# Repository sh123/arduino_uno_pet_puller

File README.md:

# Arduino plastic bottle to PET filament puller
This project is Arduino UNO/Duemilanove shield and minimalistic firmware for "Petalot PET Bottle to 3D filament" or another device with similar mechanics.

For more information about Petalot and its construction read at https://github.com/function3d/petalot.

This alternative board version based on parts and components found in a junk box, such as old Arduino UNO/Duemilanove, MX1508 stepper controller, external 12-13V power suppply, EM257 stepper from old printer, unlike origintal version it does not use WiFi remote control.

NB! PCB board is designed to be suitable for CNC milling, so some layout design decisions might look somewhat illogical.

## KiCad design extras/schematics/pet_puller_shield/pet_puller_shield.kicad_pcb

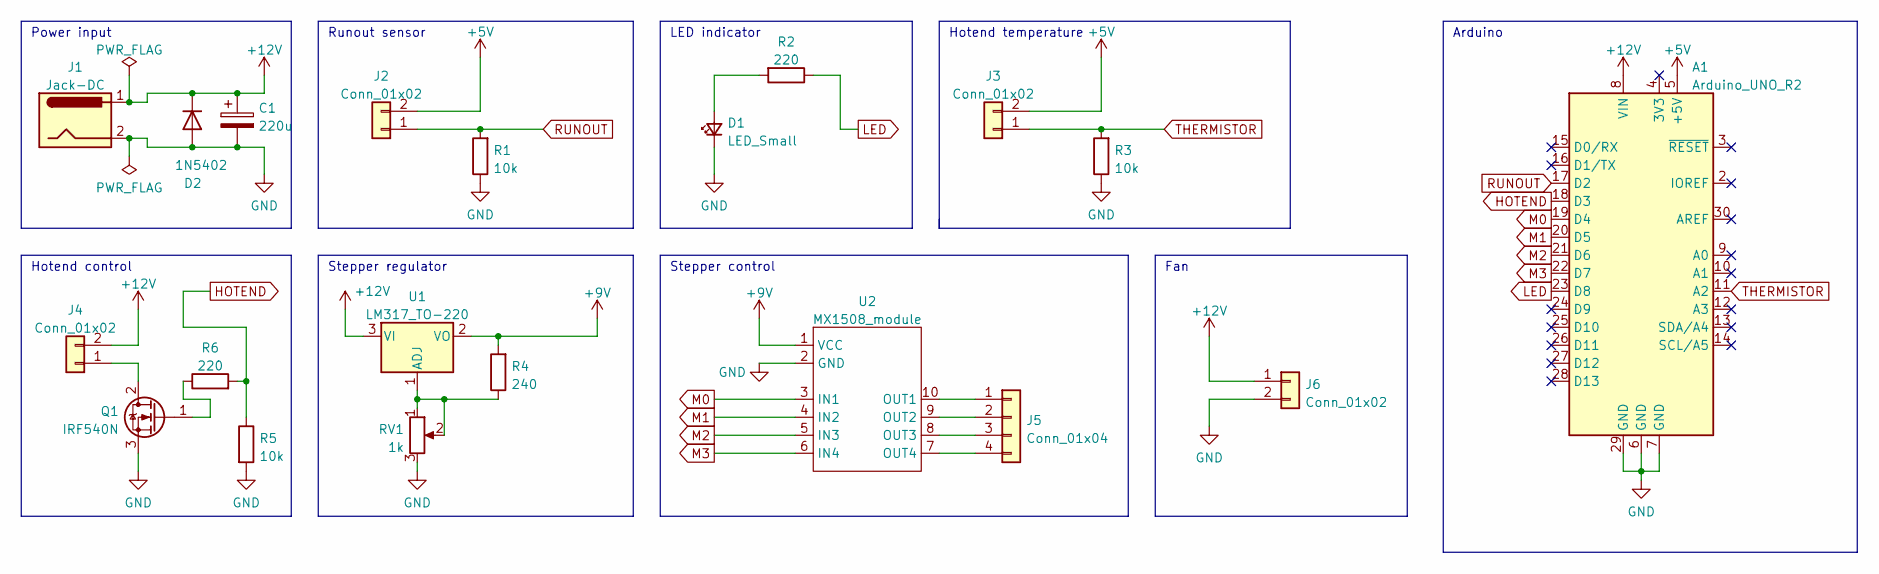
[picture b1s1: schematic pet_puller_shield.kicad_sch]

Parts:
A1: Arduino_UNO_R2
C1: 220u; CP_Radial_D8.0mm_P3.80mm
D1: LED_Small; LED_D3.0mm
D2: 1N5402; D_DO-201AD_P15.24mm_Horizontal
J1: Jack-DC; BarrelJack_GCT_DCJ200-10-A_Horizontal
J2, J3, J6: Conn_01x02; JST_EH_B2B-EH-A_1x02_P2.50mm_Vertical
J4: Conn_01x02; JST_NV_B02P-NV_1x02_P5.00mm_Vertical
J5: Conn_01x04; JST_EH_B4B-EH-A_1x04_P2.50mm_Vertical
Q1: IRF540N; TO-220-3_Horizontal_TabDown
R1, R3, R5: 10k; R_Axial_DIN0204_L3.6mm_D1.6mm_P5.08mm_Horizontal
R2, R6: 220; R_Axial_DIN0204_L3.6mm_D1.6mm_P5.08mm_Horizontal
R4: 240; R_Axial_DIN0204_L3.6mm_D1.6mm_P5.08mm_Horizontal
RV1: 1k; Potentiometer_Bourns_3339P_Vertical
U1: LM317_TO-220; TO-220-3_Horizontal_TabDown
U2: MX1508_module; mx1508_module

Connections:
+5V: A1.5 (+5V), J2.2, J3.2
+9V: R4.2, U1.2 (VO), U2.1 (VCC)
+12V: A1.8 (VIN), C1.1, D2.1 (K), J1.1, J4.2, J6.1, U1.3 (VI)
GND: A1.6 (GND), A1.7 (GND), A1.29 (GND), C1.2, D1.1 (K), D2.2 (A), J1.2, J1.3, J6.2, Q1.3 (S), R1.1, R3.1, R5.2, RV1.3, U2.2 (GND)
HOTEND: A1.18 (D3), R5.1, R6.2
LED: A1.23 (D8), R2.1
M0: A1.19 (D4), U2.3 (IN1)
M1: A1.20 (D5), U2.4 (IN2)
M2: A1.21 (D6), U2.5 (IN3)
M3: A1.22 (D7), U2.6 (IN4)
unnamed: D1.2 (A), R2.2
unnamed: J4.1, Q1.2 (D)
unnamed: J5.1, U2.10 (OUT1)
unnamed: J5.2, U2.9 (OUT2)
unnamed: J5.3, U2.8 (OUT3)
unnamed: J5.4, U2.7 (OUT4)
unnamed: Q1.1 (G), R6.1
unnamed: R4.1, RV1.1, RV1.2, U1.1 (ADJ)
RUNOUT: A1.17 (D2), J2.1, R1.2
THERMISTOR: A1.11 (A2), J3.1, R3.2

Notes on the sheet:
Fan
Stepper control
Arduino
Runout sensor
Power input
LED indicator
Hotend temperature
Hotend control
Stepper regulator

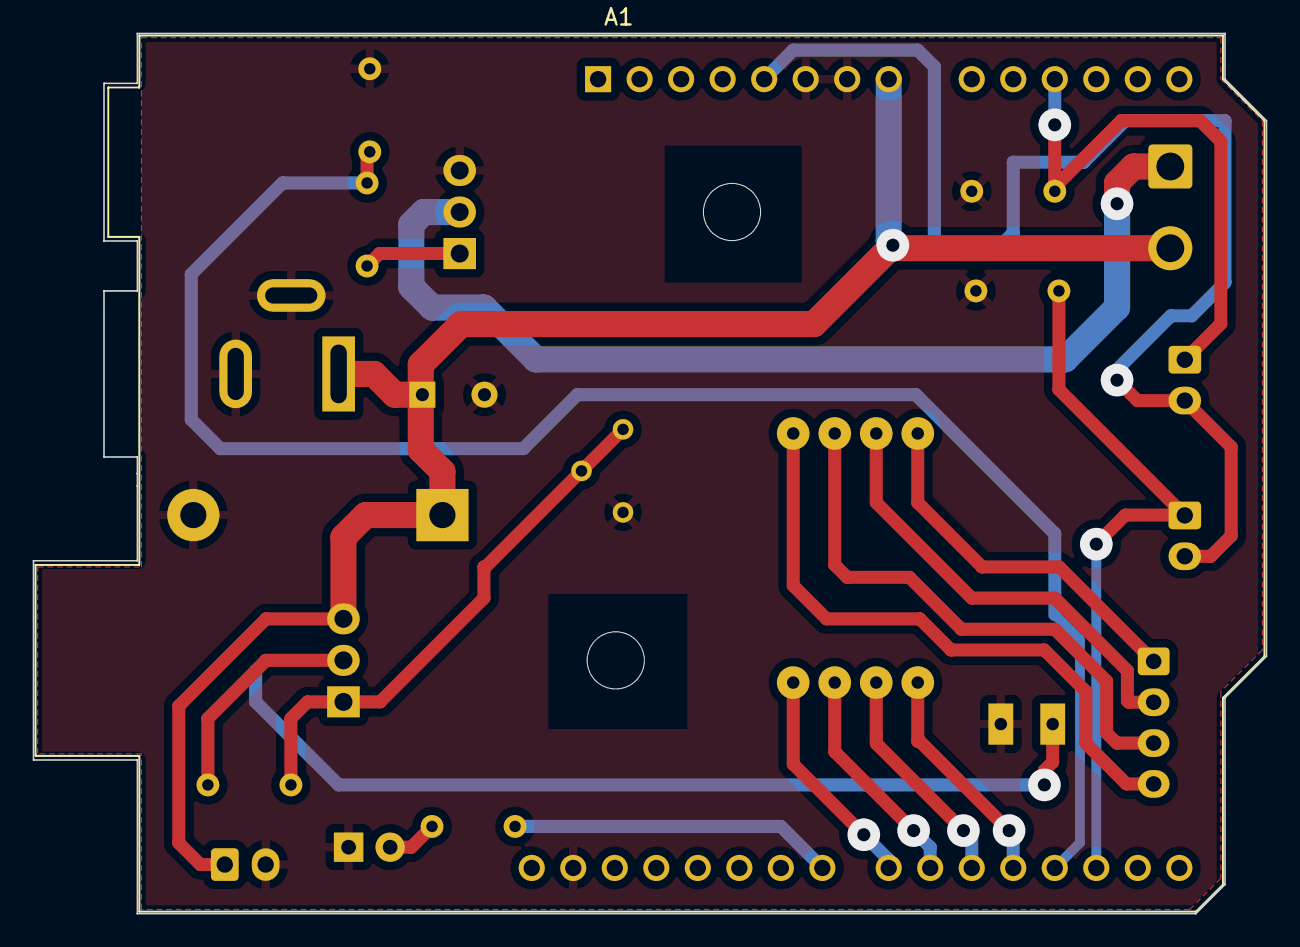
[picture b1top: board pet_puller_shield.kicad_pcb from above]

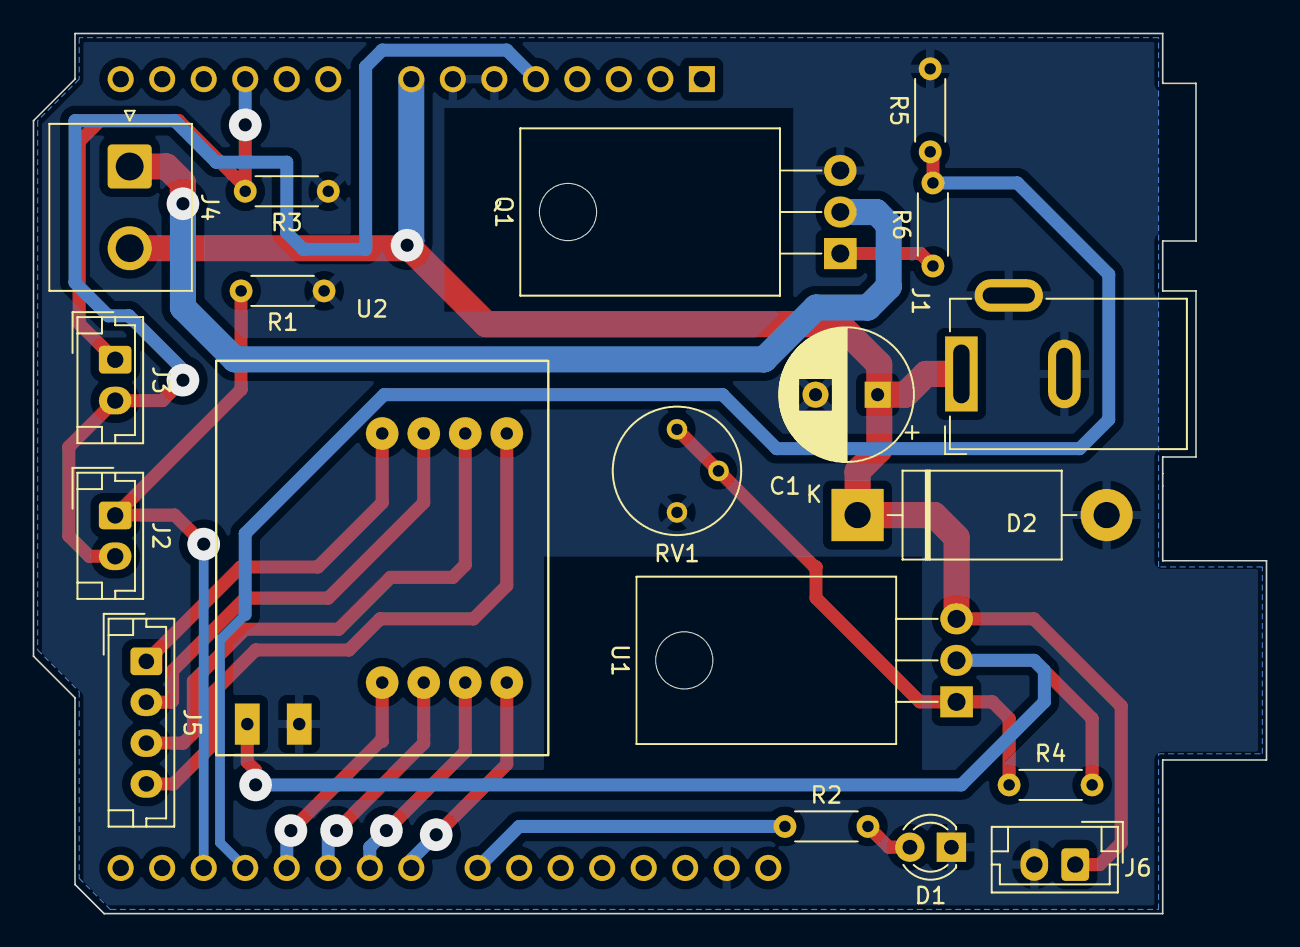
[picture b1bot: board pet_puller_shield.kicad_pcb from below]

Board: 2 copper layers, 75.4 x 53.8 mm, 20 parts (19 on the bottom side), 20 nets.

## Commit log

2025-02-02 Added .gitignore
2025-02-02 Update description
2025-02-02 Update comment
2025-02-07 Added schematics
2025-02-08 Update schematics
2025-02-08 Updated schematics
2025-02-08 Add drill files
2025-02-08 Added project files
2025-02-08 Updated schematics and gcode
2025-02-09 Updated cnc job files
2025-02-09 Update cnc jobs
2025-02-10 Update project
2025-02-11 Code update
2025-02-12 Update code
2025-02-13 Models
2025-02-14 Adjust temperature
2025-02-14 Updated gcode
2025-02-14 Updated project
2025-09-10 Added source stl models
2025-09-10 Removed unneeded file
